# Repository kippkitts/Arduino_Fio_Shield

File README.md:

Arduino_Fio_Shield
==================

For projects that require wireless control of high power devices, the Fio Shield provides a solution.  It features six IRF540 high power MOSFETS that can support 28 Amp loads, each of which is tied to a PWM enabled pin on the Arduino Fio.  This allows your Fio to interface with all sorts of high load devices (solenoids, lamps, pumps, motors, fans, etc.), and with an Xbee attached, you can control these devices remotely.  The analog pins, the rest of the digital IO pins, and the 3V3 pin of the Fio are also broken out on the shield for greater flexibility.  The Eagle CAD files for the Fio Shield are provided here.

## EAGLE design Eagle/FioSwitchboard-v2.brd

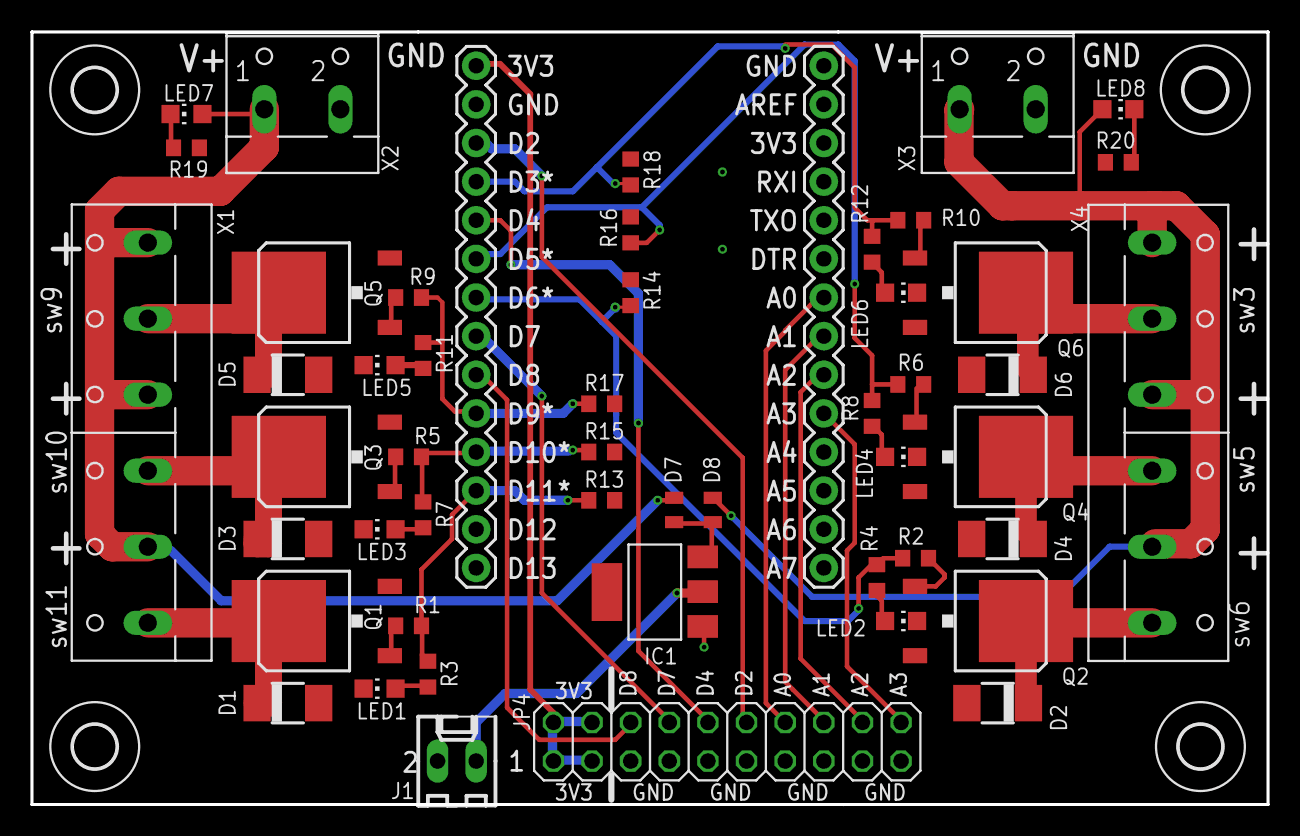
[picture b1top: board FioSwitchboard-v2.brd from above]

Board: 2 copper layers, 81.3 x 50.8 mm, 56 parts (1 on the bottom side), 40 nets.

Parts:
D1, D2, D3, D4, D5, D6: DO-214AC
D7, D8: MICROMELF-R
HOLE1, HOLE2, HOLE3, HOLE4: 2,8
IC1: REG1117; SOT223
J1: 22-27-2021-02; 6410-02
JP1, JP2: M14; 1X14
JP4: 2X10
LED1, LED2, LED3, LED4, LED5, LED6, LED7, LED8: CHIP-LED0805
Q1, Q2, Q3, Q4, Q5, Q6: IRF540SMT; D-PAK_TO252AA
R1, R2, R5, R6, R9, R10: 100R; R0603
R3, R4, R7, R8, R11, R12: 590R; R0603
R13, R14, R15, R16, R17, R18: 1M; R0603
R19, R20: 1k; R0603
U$1: EAGLE-PLC-8MM
X1, X4: W237-136
X2, X3: W237-102

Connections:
+5V: IC1.2, J1.1
A0: JP1.7, JP4.14
A1: JP1.8, JP4.16
A2: JP1.9, JP4.18
A3: JP1.10, JP4.20
D2: JP2.3, JP4.12
D3: JP2.4, R10.2, R12.2, R18.1
D4: JP2.5, JP4.10
D5: JP2.6, R6.2, R8.2, R16.1
D6: JP2.7, R2.2, R4.2, R14.1
D7: JP2.8, JP4.8
D8: JP2.9, JP4.6
D9: JP2.10, R9.2, R11.2, R17.1
D10: JP2.11, R5.2, R7.2, R15.1
D11: JP2.12, R1.2, R3.2, R13.1
GND: D1.A, D2.A, D3.A, D4.A, D5.A, D6.A, IC1.1, J1.2, JP1.1, JP2.2, JP4.5, JP4.7, JP4.9, JP4.11, JP4.13, JP4.15, JP4.17, JP4.19, LED1.C, LED2.C, LED3.C, LED4.C, LED5.C, LED6.C, Q1.3, Q2.3, Q3.3, Q4.3, Q5.3, Q6.3, R13.2, R14.2, R15.2, R16.2, R17.2, R18.2, R19.2, R20.2, X2.2, X3.2
unnamed: Q3.1, R5.1
unnamed: Q5.1, R9.1
unnamed: D2.C, Q2.4, X4.6
unnamed: LED2.A, R4.1
unnamed: Q6.1, R10.1
unnamed: D3.C, Q3.4, X1.3
unnamed: LED3.A, R7.1
unnamed: Q4.1, R6.1
unnamed: D4.C, Q4.4, X4.4
unnamed: LED4.A, R8.1
unnamed: Q2.1, R2.1
unnamed: D5.C, Q5.4, X1.5
unnamed: LED5.A, R11.1
unnamed: D1.C, Q1.4, X1.1
unnamed: Q1.1, R1.1
unnamed: LED1.A, R3.1
unnamed: D6.C, Q6.4, X4.2
unnamed: LED6.A, R12.1
unnamed: D7.C, D8.C, IC1.3
unnamed: LED7.C, R19.1
unnamed: LED8.C, R20.1
V+: D8.A, LED8.A, X3.1, X4.1, X4.3, X4.5
VCC: JP2.1, JP4.1, JP4.2, JP4.3, JP4.4
VDD: D7.A, LED7.A, X1.2, X1.4, X1.6, X2.1

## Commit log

2014-03-26 Add Eagle Files
